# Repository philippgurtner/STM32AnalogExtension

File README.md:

# STM32AnalogExtension
In diesem Repository befinden sich die Daten für eine analog Erweiterung, bestehend aus einem externen ADC für das STM32F0-Discovery Board. 
Im weiteren ist die komplette Dokumentation, so dass die Projektschritte verstanden werden können und auch das Projekt verständlich wird. 

Das Projekt ist OpenSource & darf frei verwendet (und so auch gerne verbessert) werden. 
Ich hoffe viel Freude damit zu bereiten. 
:)

# Projektdokumentation

## Aufgabe
Für die Bereichsübergreifende Projekte der Schule sollte eine Erweiterung für das STM32F051Discovery Kit erstellt werden. 
Dieses Projekt ist eine Analoge Erweiterung mit einem 24Bit 4kSps externen ADC. Dabei ist wichtig dass die Erweiterung mit SPI Angesteuert wird. 
Mehr im Fokus des Projektes stand die Einfachheit, so das das Produkt einfach angewendet werden kann, als es Sehr genau ist. 
So wurde bei der Temperaturmessung auf die Konstantstromquelle Verzichtet, jedoch können zukünftige Anwender die tolle Auflösung mit allen Problemen und Hürden selbst erfahren. 

### Vorgaben
-	Es soll nur eine Seite für Anschlüsse genutzt werden
-	Die Erweiterungsplatine sitzt also zur rechten oder linken Seite des STM32F0-Board
-	Die Seite wird durch die Versorgungsspannung vorgegeben, wenn möglich 3V
-	Platinendicke 1,6mm
-	Lagenanzahl: 2
-	Bestückungsdruck: Schriftgrösse 1mm  Name der Bauteile, Stecker Pin 1, Signalnamen Stecker 
    - 2mm Name Projekt, Datum, Namen der Ersteller
-	Line Space ≥200μm
-	GND-Plane
-	Abmessung Discovery-Board: 33Pin Header

### Zielsetzung
- Das Board muss passend als Erweiterung für das Devboard sein, so dass es einfach adaptiert werden kann. 
- Die Hauptanwendung besteht darin einen 3-Leiter PT100 zu messen.
- Weiter soll möglich sein, durch eine Buchse eine eigene Messspannung hinzuzuführen, so dass auch diese digitalisiert werden kann. 
- Durch einen hochauflösenden ADC (>16Bit) werden dann hohe Genauigkeiten möglich.

## Grundlagen
### Analog-Digital-Converter (ADC)
Die Aufgabe eines ADC’s, ist die Umwandlung von analogen Signalen zu digitalen Daten. Dabei sind mehrere Faktoren wichtig, wie SampleRate und Auflösung (Bittiefe). Um die Signale zu ermitteln müssen wir wissen, was für eine Auflösung der ADC hat. Denn mit diesem, wissen wir wie fein wir das analoge Signal aufteilen können und so die digitalen Werte erhalten. Anhand der SampleRate sehen wir, wie viel Mal der ADC in der Sekunde das analoge Signal maximal abtasten kann. Mit diesen beiden Werten können wir dann in der Software die Werte in unser Signal umrechnen.
### Temperatursensorschaltungen

Um einen Temperatursensor anzuschliessen gibt es verschiedene Möglichkeiten. Diese sind für thermisch abhängige Widerstände, welche als Temperatursensoren funktionieren. Zum Beispiel PT100 oder PT1000. 

#### Zweileiter-Messung
Der Messwiderstand (Temperatursensor) wird über dieselbe Leitung gespiesen wie auch die Temperatur gemessen wird. Daher, dass über die Leitungen ebenfalls etwas Spannung abfällt, wird dieser Fehler nicht mit einberechnet und wird zu einem Messfehler. 
#### Dreileiter- Messung
Bei der Dreileitermessung wird der Messwiderstand über eine zusätzliche Leitung mit Strom versorgt. Daher fällt einerseits der Messfehler der Spannung weg, da die Temperatur über eine unbelastete Leitung gemessen werden kann. Da der Strom I=0A auf der Messleitung ist kann auf der gemeinsamen Leitung der Messfehler herausgerechnet werden -> Siehe Anwendung. 
#### Vierleiter- Messung
Bei einer Vierleitermessung werden der Messstrom und die Messspannung je auf einer separaten Leitung geführt. So kann der Widerstand komplett ohne Spannungsabfall auf der Messleitung gemessen werden.

## Evaluation
###	ADC
Beim Evaluieren eines ADC’s gibt es sehr viele Möglichkeiten. Die wichtigsten Eigenschaften sind Auflösung (Bittiefe) und Geschwindigkeit (Samples per Second). 
Für dieses Projekt spielt die Geschwindigkeit keine grosse Rolle, da Prozesswerte abgefragt werden möchten und es sich nicht um eine Digitalisierung eines hochfrequenten Signals handelt. 
Die Auflösung spielt für dieses Projekt die grössere Rolle. Da gezeigt werden möchte wie genau der ADC ist, soll die Temperatur des Temperatursensors ohne jegliche Verstärkung gemessen werden. 
Die Berechnungen zu der Temperaturauflösung sind in Tabelle 1 zu finden. \todo

### Temperatursensor
Als Temperatursensor eignet sich ein thermisch abhängiger Widerstand sehr gut. Diese werden oft auch in Industrieanlagen verwendet. Da gerade ein fertiger PT100 Sensor an Lager ist wird dieser Verwendet, er benötigt nur eine Buchse auf der Platine um den Sensor anzuhängen. 
###	Weitere Anschlüsse
Als zusätzliche Anschlüsse wurden BNC Buchsen ausgewählt. Durch ihre Standardisierung und häufigen gebrauch eignen sie sich gut um weitere Signale anzulegen und zu messen. 
Es können dann entweder Oszilloskop-Messspitzen oder auch Adapter auf andere Hochfrequenz Stecker, wie auch auf Bananenbuchse verwendet werden. 

## Schaltungsaufbau
### 3-Leitermessung
Für diese Schaltung wird eine Dreileiter-Messung für den Temperatursensor verwendet, da diese sehr einfach aufzubauen, wie auch dann interessant zu verarbeiten ist. Weiter sind hier nur 3 ADC Kanäle nötig obwohl wie bei einer 4-Leiter Messung auch der Widerstand der Messleitung herausgerechnet werden kann.  
### ADC-Serial Interface
Der ADC besitzt ein Serial Peripherie Interface (SPI). Über diese kann mit dem Microcontroller kommuniziert werden. Damit die Peripherie nicht per Bit-Banging angesteuert werden muss, müssen die SPI-Anschlüsse beim Microcontroller an einen SPI fähigen Port geroutet werden.
### Funktion der Schaltung / Überlegungen
Dank folgender Rechnung wird ersichtlich wie die Spannung über dem PT100 berechnet werden kann. Dies funktioniert nach der theoretischen Betrachtung in Abbildung 4.
Es werden hier alle anderen Spannungen herausgerechnet. 

## Auswertung V0.1 
### Hardware
Während der Lötarbeit konnten wir nichts Auffälliges erkennen, was beim Löten problematisch werden könnte. Erst beim Konfigurieren der SPI-Schnittstelle mit der STM32CubeMX-Software, haben wir festgestellt, dass die SPI-Schnittstelle nicht frei auf alle Pins mapbar ist, wie wir das fälschlicherweise aus dem Datenblatt gelesen haben.
Somit müssen am Schema noch einige Anpassungen gemacht werden. Weiter haben wir auch während der Bearbeitung gemerkt, dass der ADC mit Differenzmessung arbeitet. Dies bedeutet, er misst die Differenz zwischen zwei Kanälen. Möchte man eine Spannung absolut messen, so muss dies mit einer Differenzmessung zu Masse erfolgen. Der Chip bietet die Möglichkeit im INPMUX-Register als negative Referenz den AINCOM-Pin zu verwenden, der aber mit Masse verbunden sein sollte.
Für die ersten Versuche mit dem Prototyp haben wir die Kontakte auf der Leiterplatte korrigiert, so dass wir Tests durchführen konnten. Als Erweiterung für die nächste Version wäre zusätzlich eine Stiftleiste vorzusehen, dass die SPI-Analyse einfacher mit einem Logicanalyzer erfolgen kann. Dies hat auch einen Vorteil für den späteren Unterricht, so kann die SPI-Schnittstelle einfacher analysiert werden. 

In der nachfolgenden Tabelle sind die Leiterplattenänderungen festgehalten:

|    WAS                       |    von                 |    Nach                                        |    div.                                                                                                          |
|------------------------------|------------------------|------------------------------------------------|------------------------------------------------------------------------------------------------------------------|
|    Clock                     |    PA4                 |    PA5                                         |    SPI                                                                                                           |
|    MOSI                      |    PA5                 |    PA7                                         |    SPI                                                                                                           |
|    CS                        |    PA7                 |    PF5                                         |    SPI                                                                                                           |
|    AINCOM                    |    Nc                  |    GND                                         |    Differenzmessung                                                                                              |
|    Stiftleiste               |                        |                                                |    Für Debugging / SPI-Analyse                                                                                   |
|    Widerstände   R12-R14     |    Eingang von ADC     |    weglassen                                   |    Können Störungen auf   Messleitung verursachen                                                                |
|    BNC-Abschwächer           |    2.2k Ohm            |    Spannungsteiler mit 47kOhm und   2.2kOhm    |    Somit können Eingangsspannungen   bis zu 50V angelegt werden und nicht nur 2.5V über die Interne Referenz     |
|    5.08mm   schraubklemme    |    Weglassen           |                                                |    So können die Temperatursignale   direkter und präziser geroutet werden. Der Stecker wird nicht benötigt.     |
|    Kondensatoren   1uF       |    AIN0, AIN1, AIN2    |    GND                                         |    Filterung der Temp Messung                                                                                    |
|    Kondensator   1uF         |    AIN0                |    AIN1                                        |    Filterung der Temp Messung                                                                                    |                                                                         |   |

## Softwarerealisierung 
### Konfiguration mit STM32CubeMX
Vorzunehmende Konfigurationen in STM32CubeMX, um die SPI-Schnittstelle zu verwenden: 
Beim Starten das STM32F0-Discovery Board auswählen, so werden die Taster und LEDs richtig initialisiert
-   Pinout & Konfiguration:
    - Pin-Konfiguration
        - PF5: 	ADC_CS
        - PC4: 	ADC_START
        - PC5: 	ADC_RESET
        - PB0: 	ADC_DRDY
    - Modul Connectivity --> SPI1 hinzufügen
        - Data Size: 	8Bit
        - Prescaler:
        - First Bit: 	MSB First
        - Clock Polarity (CPOL): 	LOW
        - Clock Phase (CPHA): 		2 Edge
- Project Manger
    - Code Generator
    - Generate Files: Generate peripheral initialization as a pair... 
        (So wird nicht eine lange main.c-Datei erzeugt)

### Verwenden von HAL-Library 
Hardware Abstraction Librarys, kurz HAL, dienen dazu unabhängig von der verwendeten Hardware, eine Software zu schreiben. So kann eine mit HAL geschriebene Software einfach auf ein anderes System portiert werden und das System übernimmt die Hardwaresteuerung, so dass der Nutzercode nicht (gross) angepasst werden muss. So wird zum Beispiel das Schreiben eines Pins ganz einfach, man muss sich nicht mehr überlegen wo der gerade angeschlossen ist, man benutzt einfach das Userlabel zum Pin. 
```c
HAL_GPIO_WritePin(ADC_CS_GPIO_Port, ADC_CS_Pin,X)
// X=1 --> Ausgang wird auf 1 gesetzt
// X=0 --> Ausgang wird auf 0 gesetzt
```

### SPI-Analyse mit Logicanalyzer

Erweiterungen siehe Anhang
In vielen Fällen kann es hilfreich sein, wenn man mit einem Busprotokoll arbeitet, dieses auch zu messen. Es stand uns dazu ein PicoScope6 zur Verfügung. Sie können bis zu 16 Digitalanalysen und 2 Analoganalysen machen. Es ist ein Oszilloskop ohne Bildschirm. In der Software (Für Windows, MacOS und Linux) kann man das PicoScope steuern. Folgend unsere Erfahrungen. 
Im Anhang befindet sich eine Anleitung wie man eine Analyse der SPI Daten machen kann.

## Softwarefunktionen
Einen kurzen Einblick in die Funktionen welche eingesetzt werden. Weitere Details können dem Code entnommen werden. 
### Registermanipulation
Zum Schreiben und lesen von Registern gibt es die Funktionen (Auszug .h File): 

\todo

Wenn nur ein Register gelesen / geschrieben werden muss, so kann jeweils die ADCreg**** Funktion benutzt werden
### Commands
Der ADC kann über verschiedene Kommandos gesteuert werden. Diese sind alle in der "ADS1204S0x.h" Datei definiert.
```c
void ADCsendCommand(uint8_t op_code);
```
Der Funktion können die Verschiedenen op_codes mitgegeben werden. 

### Berechnungsfunktionen
#### ADC Werte auslesen
Um die Spannung über dem PT100 zu berechnen, werden alle Spannungen der drei ADC`s ausgelesen. Wie hier dargestellt messen die ADC`s folgende Spannungen:

```math
\mathrm{ADC0}=U_{\mathrm{Leiter}}+U_{\mathrm{PT100}}+U_{\mathrm{Leiter}}+U_{\mathrm{Mess}}\bigm\mathrm{ADC1}=U_{\mathrm{Leiter}}+U_{\mathrm{Mess}}\bigm\mathrm{ADC2}=U_{\mathrm{Mess}}\bigmU_{\mathrm{PT100}}=\mathrm{ADC0}-2\times U_{\mathrm{Leiter}}-U_{\mathrm{Mess}}\bigmU_{\mathrm{PT100}}=\mathrm{ADC0}-2\times\left(\mathrm{ADC1}-\mathrm{ADC2}\right)-\mathrm{ADC2\bigm}U_{\mathrm{PT100}}=\mathrm{ADC0}-2\times\mathrm{ADC1}+\mathrm{ADC2}
```
### Dimensionierungen und Berechnungen
Als Temperatursensor wird ein PT100 verwendet. Nach Spezifikation hat der Temperatursensor bei 0°C einen 100Ω Widerstand. Je nach Temperatur verändert sich der Widerstand, nach einer bestimmten Kurve. 
Als Messstrom wird bei 0°C 0.5mA verwendet. Da sich der Temperatursensor selbst erwärmt darf dieser Messstrom nicht zu hoch gewählt werden.
Um den geflossenen Strom durch den ADC zu messen, wird über einem präzisen Referenzwiderstand die Spannung gemessen, welche vom Messstrom erzeugt wird.

Anschlüsse:
Es wurde eine Temperaturmessung mittels PT100 3-Leiter Widerstand vorgenommen. 
Als zusätzliche Anschlüsse wurden BNC Buchsen ausgewählt. Durch ihre Stndrdisierung und often gebrauch eignen sie sich um weitere Signale anzulegen und zu messen. 

# Schaltungsaufbau
## ADC-Serial Interface
Der ADC besitzt ein Serial Peripherie Interface (SPI). Über dies kann mit dem Microntroller Komunizieren. 
Damit die Peripherie nicht per Bit-Banging angesteuert werden muss, müssen sie beim Microcontroller mit bei einem SPI fähigen Port verbunden werden.
# Dimensionierung
Als Temperatursensor wird ein TP100 verwendet. Nach Spezifikation hat der Temperatursensor bei 0°C 100R Widerstand. Je nach Temperaturänderung verändert sich der Widerstand nach einer Spezifizierten Kurve. 
Als Messstrom wird bei 0°C 0.5mA verwendet. Da sich der Temperatursensor selbst erwärmt darf dieser Messstrom nicht zu hoch gewählt werden. 

Um den Geflossenen Strom durch den ADC zu messen wird über einem Refererenzwiderstand die Spannung gemessen welche vom Messstrom erzeugt wird. 

# Einführung Picoscope

Das Picoscope ist ein Logicanalyser. Mit ihm ist es Möglich mehrere Digitale Signale zu Analysieren und die Daten auszuwerten. Um Herauszufinden ob die Serielle Kommunikation richtig Funktioniert kann man mit diesem Hilfsmittel einfacher messen und die Daten analysieren. 

## Vorbereitung

Um Das Picoscope an einem PC benutzen zu können sind einige Schritte notwendig. 

### Installieren der Software

Die Software kann auf der Webseite von Picosope unter > Downloads heruntergeladen werden. 
Hier muss die Genaue Modelbezeichung angegeben werden. (Wir verwendeten das Picoscope der Schule [*PicoScope 2206B MSO*](https://www.picotech.com/downloads/_lightbox/picoscope-6))

### Anschliessen der Digitalen Kanäle

Die Digitalen Kanäle befinden sich beim 16-Pin Stecker in der Mitte. Das Mitgelieferte Kabel dient um mit dem UC Board zu verbinden. 

### Einrichten der Software

1. Digitale Kanäle Gruppen

   1. Kanal Auswählen

   2. Kanal intelligent benennen

2. Hinzufügen eines Seriellen Encoders:

   1. Werkzeuge > Serielle Entschlüsselung -> Erstellen > SPI >

3. Setzen des Triggers (In der untersten Leiste)
   1. Trigger: Einzeln
   2. In den Triggereinstellungen (Rechts vom Trigger) kann auf Digital > CS Pos Flanke gesetzt werden
   3. Start

## SPI Analyse

Mit den Empfangen Daten lässt sich verstehen was in SPI gesendet wird

Folgend im Code und Als Analyse:

MISO, Die Daten werden vom Master an den Slave gesendet. Die Rückgabe des Slaves ist nicht wichtig. 

```c
HAL_GPIO_WritePin(ADC_CS_GPIO_Port, ADC_CS_Pin,0);

uint8_t au8_txdata = {0x42,		// Register INPMUX_REG_ADDR (0x02) | Write command 0x40
                      0,		// Write length -1 = 0
                      0x3C};	// Data = ADS_P_AIN3 (0x30)+ ADS_N_AINCOM (0x0C)		
HAL_SPI_Transmit(&hspi1,au8_txdata,3,10);
HAL_GPIO_WritePin(ADC_CS_GPIO_Port, ADC_CS_Pin,1);
```

# Variablen Viewer installieren (debuggen)

Das STMStudio ermöglicht es eine *debug Datei zu Importieren und diese Laufen zu lassen. So können mehrere globale Variablen angesehen werden. So kann eine Langzeitanalyse des Verhalten gemacht werden. 

- STM-STUDIO-STM32 (von https://www.st.com/en/development-tools/stm-studio-stm32.html ) installieren (benötigt Java https://www.java.com/de/download/win10.jsp)

- STM Studio öffnen

- "File" > "Import variables from executable" öffnen
  - "Executable file" .elf Datei suchen (im STM Projekt unter "Debugger")
  - (Warnung Ignorieren)
  - Variable zum Monitoren auswählen 
  - "Import" , "Close"

- Variable (Display Variables) in Viewer hineinziehen (Drag and Drop)

- Start Knopf drücken (Debugger aus IDE darf nicht gleichzeitig aktiv sein)

- Im Viewer: Rechtsklick, "Autorange" > "Both Axis"

- Eventuell als Balken darstellen, maximum wert beachten (über hex ganz einfach manuell einstellbar)

# Sorry, die vollständige Dokumentation ist Leider nicht Opensource (und vorallem .docx), jedoch wird das Projekt bei Gelegenheit hier noch zu ende Dokumentiert (natürlich in MD :) , Danke für die Geduld)

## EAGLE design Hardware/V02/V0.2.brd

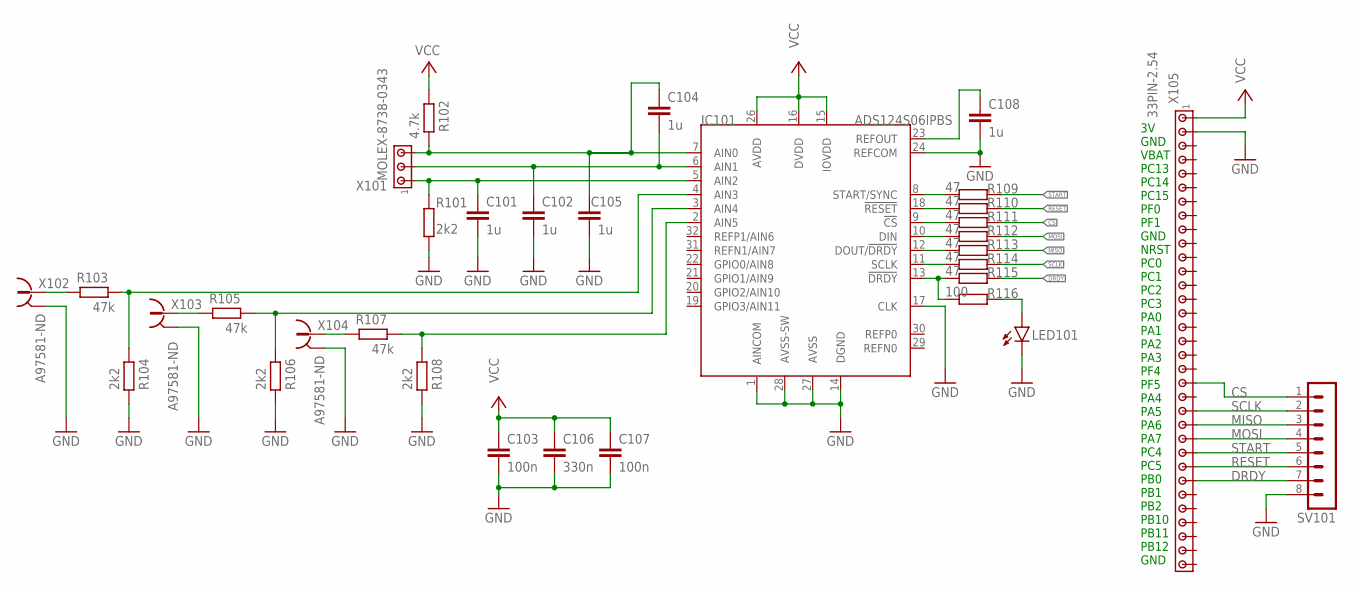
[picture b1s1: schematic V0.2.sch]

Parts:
C101, C102, C104, C105, C108: 1u; C0603; DIGIKEY_NR 1276-1182-1-ND
C103, C107: 100n; C0603; DIGIKEY_NR 1276-6439-1-ND
C106: 330n; C0603; DIGIKEY_NR 490-6050-1-ND
IC101: ADS124S06IPBS; TQFP32-05; DIGIKEY_NR 296-45188-ND
LED101: LEDSML0603; SML0603; DIGIKEY_NR 475-3118-1-ND
R101, R104, R106, R108: 2k2; R0805W; DIGIKEY_NR 408-1635-1-ND
R102: 4.7k; R0603; DIGIKEY_NR 311-4.70KHRCT-ND
R103, R105, R107: 47k; R0603; DIGIKEY_NR P123333CT-ND
R109, R110, R111, R112, R113, R114, R115: 47; R0603; DIGIKEY_NR 311-470GRCT-ND
R116: 100; R0603; DIGIKEY_NR 311-100DCT-ND
SV101: MA08-1; DIGIKEY_NR 732-5321-ND
X101: MOLEX-8738-0343; MOLEX-87438-0343; DIGIKEY_NR WM7647CT-ND
X102, X103, X104: A97581-ND; 1634503; DIGIKEY_NR A97581-ND
X105: 33PIN-2.54; 1X33; DIGIKEY_NR 609-2223-ND

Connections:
AIN0: C104.1, C105.1, IC101.7 (AIN0), R102.1, X101.3, X101.3_1 (3)
AIN1: C102.1, C104.2, IC101.6 (AIN1), X101.2, X101.2_1 (2)
AIN2: C101.1, IC101.5 (AIN2), R101.2, X101.1, X101.1_1 (1)
CS: R111.2, SV101.1, X105.20
DRDY: R115.2, SV101.7, X105.27
GND: C101.2, C102.2, C103.2, C105.2, C106.2, C107.2, C108.2, IC101.1 (AINCOM), IC101.14 (DGND), IC101.17 (CLK), IC101.24 (REFCOM), IC101.27 (AVSS), IC101.28 (AVSS-SW), LED101.C, R101.1, R104.1, R106.1, R108.1, SV101.8, X102.2, X102.3 (2), X102.4 (2), X102.5 (2), X103.2, X103.3 (2), X103.4 (2), X103.5 (2), X104.2, X104.3 (2), X104.4 (2), X104.5 (2), X105.2
MISO: R113.2, SV101.3, X105.23
MOSI: R112.2, SV101.4, X105.24
unnamed: IC101.8 (START/SYNC), R109.1
unnamed: IC101.18 (!RESET), R110.1
unnamed: IC101.9 (!CS), R111.1
unnamed: IC101.10 (DIN), R112.1
unnamed: IC101.12 (DOUT/!DRDY), R113.1
unnamed: IC101.11 (SCLK), R114.1
unnamed: IC101.13 (!DRDY), R115.1, R116.1
unnamed: IC101.4 (AIN3), R103.1, R104.2
unnamed: R103.2, X102.1
unnamed: R105.2, X103.1
unnamed: LED101.A, R116.2
unnamed: C108.1, IC101.23 (REFOUT)
unnamed: R107.2, X104.1
unnamed: IC101.3 (AIN4), R105.1, R106.2
unnamed: IC101.2 (AIN5), R107.1, R108.2
RESET: R110.2, SV101.6, X105.26
SCLK: R114.2, SV101.2, X105.22
START: R109.2, SV101.5, X105.25
VCC: C103.1, C106.1, C107.1, IC101.15 (IOVDD), IC101.16 (DVDD), IC101.26 (AVDD), R102.2, X105.1

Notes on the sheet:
3V GND VBAT PC13 PC14 PC15 PF0 PF1 GND NRST PC0 PC1 PC2 PC3 PA0 PA1 PA2 PA3 PF4 PF5 PA4 PA5 PA6 PA7 PC4 PC5 PB0 PB1 PB2 PB10 PB11 PB12 GND

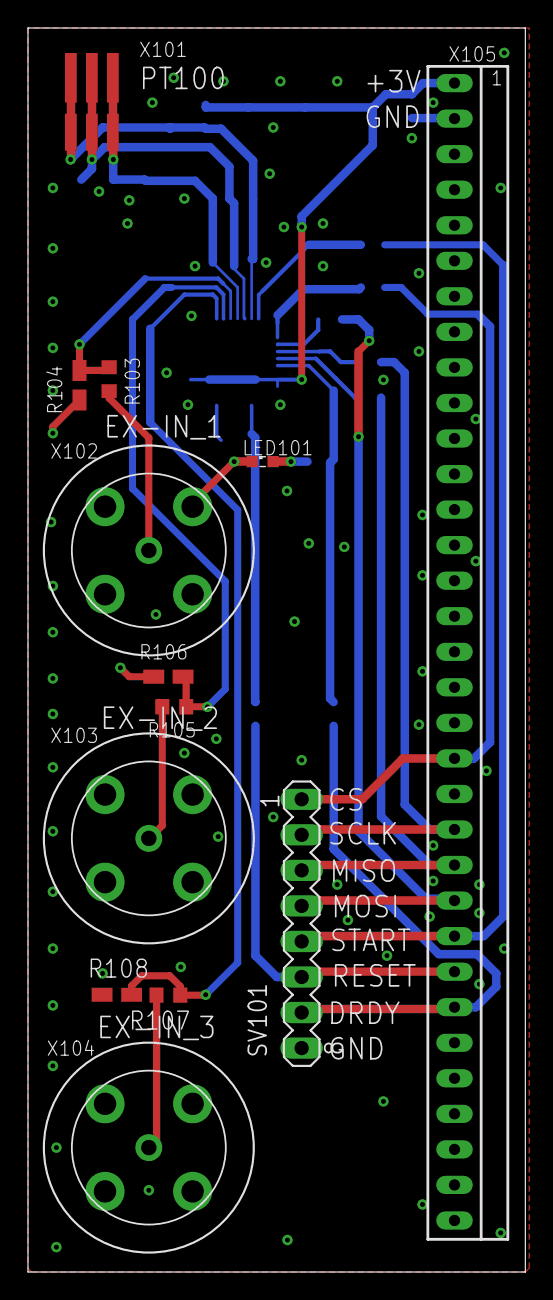
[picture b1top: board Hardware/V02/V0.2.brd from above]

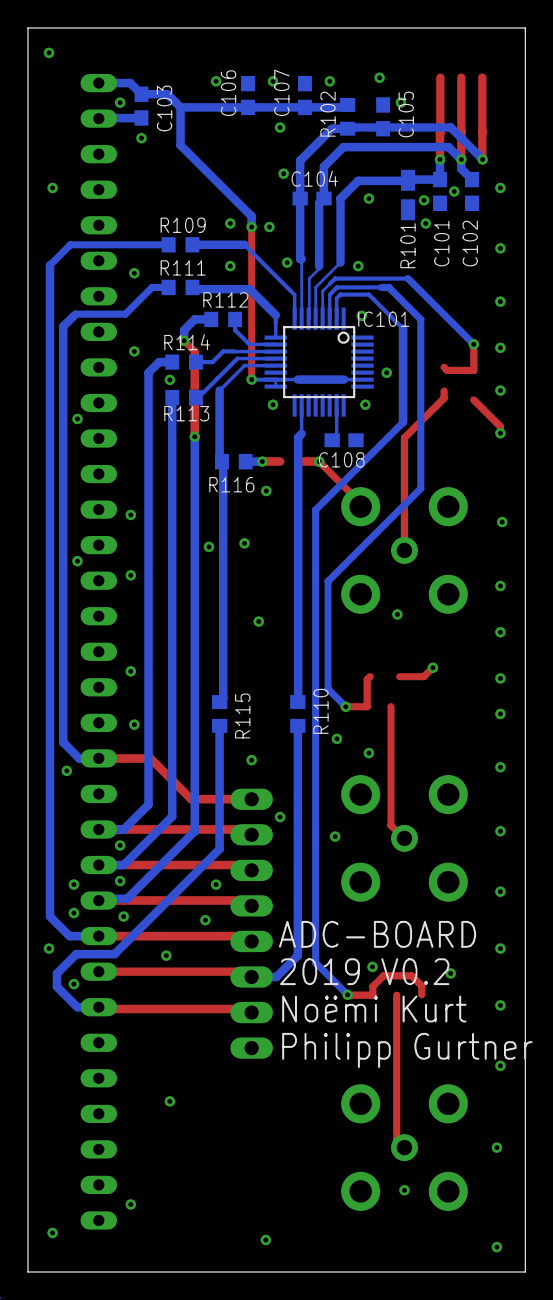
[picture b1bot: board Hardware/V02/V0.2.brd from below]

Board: 2 copper layers, 35.5 x 88.9 mm, 32 parts (19 on the bottom side), 27 nets.

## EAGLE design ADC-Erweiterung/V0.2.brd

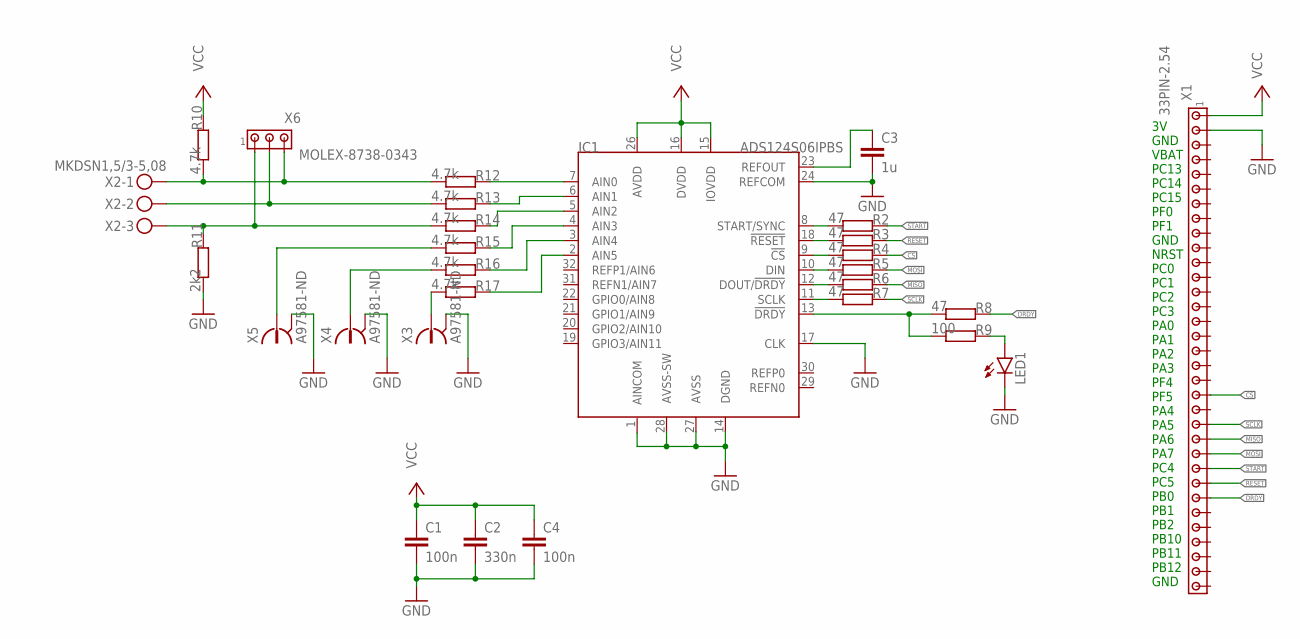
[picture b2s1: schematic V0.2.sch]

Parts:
C1, C4: 100n; C0603; DIGIKEY_NR 1276-6439-1-ND
C2: 330n; C0603; DIGIKEY_NR 490-6050-1-ND
C3: 1u; C0603; DIGIKEY_NR 1276-1182-1-ND
IC1: ADS124S06IPBS; TQFP32-05; DIGIKEY_NR 296-45188-ND
LED1: LEDSML0603; SML0603; DIGIKEY_NR 475-3118-1-ND
R2, R3, R4, R5, R6, R7, R8: 47; R0603; DIGIKEY_NR 311-470GRCT-ND
R9: 100; R0603; DIGIKEY_NR 311-100DCT-ND
R10, R12, R13, R14, R15, R16, R17: 4.7k; R0603; DIGIKEY_NR 311-4.70KHRCT-ND
R11: 2k2; R0805W; DIGIKEY_NR 408-1635-1-ND
X1: 33PIN-2.54; 1X33; DIGIKEY_NR 609-2223-ND
X2: MKDSN1,5/3-5,08; DIGIKEY_NR 277-14503-ND
X3, X4, X5: A97581-ND; 1634503; DIGIKEY_NR A97581-ND
X6: MOLEX-8738-0343; MOLEX-87438-0343; DIGIKEY_NR WM7647CT-ND

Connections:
CS: R4.2, X1.20
DRDY: R8.2, X1.27
GND: C1.2, C2.2, C3.2, C4.2, IC1.1 (AINCOM), IC1.14 (DGND), IC1.17 (CLK), IC1.24 (REFCOM), IC1.27 (AVSS), IC1.28 (AVSS-SW), LED1.C, R11.1, X1.2, X3.2, X3.3 (2), X3.4 (2), X3.5 (2), X4.2, X4.3 (2), X4.4 (2), X4.5 (2), X5.2, X5.3 (2), X5.4 (2), X5.5 (2)
MISO: R6.2, X1.23
MOSI: R5.2, X1.24
unnamed: IC1.8 (START/SYNC), R2.1
unnamed: IC1.18 (!RESET), R3.1
unnamed: IC1.9 (!CS), R4.1
unnamed: IC1.10 (DIN), R5.1
unnamed: IC1.12 (DOUT/!DRDY), R6.1
unnamed: IC1.11 (SCLK), R7.1
unnamed: IC1.13 (!DRDY), R8.1, R9.1
unnamed: R10.1, R12.1, X2.1, X6.3, X6.3_1 (3)
unnamed: R13.1, X2.2, X6.2, X6.2_1 (2)
unnamed: R11.2, R14.1, X2.3, X6.1, X6.1_1 (1)
unnamed: R15.1, X5.1
unnamed: IC1.3 (AIN4), R16.2
unnamed: IC1.2 (AIN5), R17.2
unnamed: LED1.A, R9.2
unnamed: C3.1, IC1.23 (REFOUT)
unnamed: IC1.4 (AIN3), R15.2
unnamed: R16.1, X4.1
unnamed: R17.1, X3.1
unnamed: IC1.5 (AIN2), R14.2
unnamed: IC1.7 (AIN0), R12.2
unnamed: IC1.6 (AIN1), R13.2
RESET: R3.2, X1.26
SCLK: R7.2, X1.22
START: R2.2, X1.25
VCC: C1.1, C2.1, C4.1, IC1.15 (IOVDD), IC1.16 (DVDD), IC1.26 (AVDD), R10.2, X1.1

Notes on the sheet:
3V GND VBAT PC13 PC14 PC15 PF0 PF1 GND NRST PC0 PC1 PC2 PC3 PA0 PA1 PA2 PA3 PF4 PF5 PA4 PA5 PA6 PA7 PC4 PC5 PB0 PB1 PB2 PB10 PB11 PB12 GND

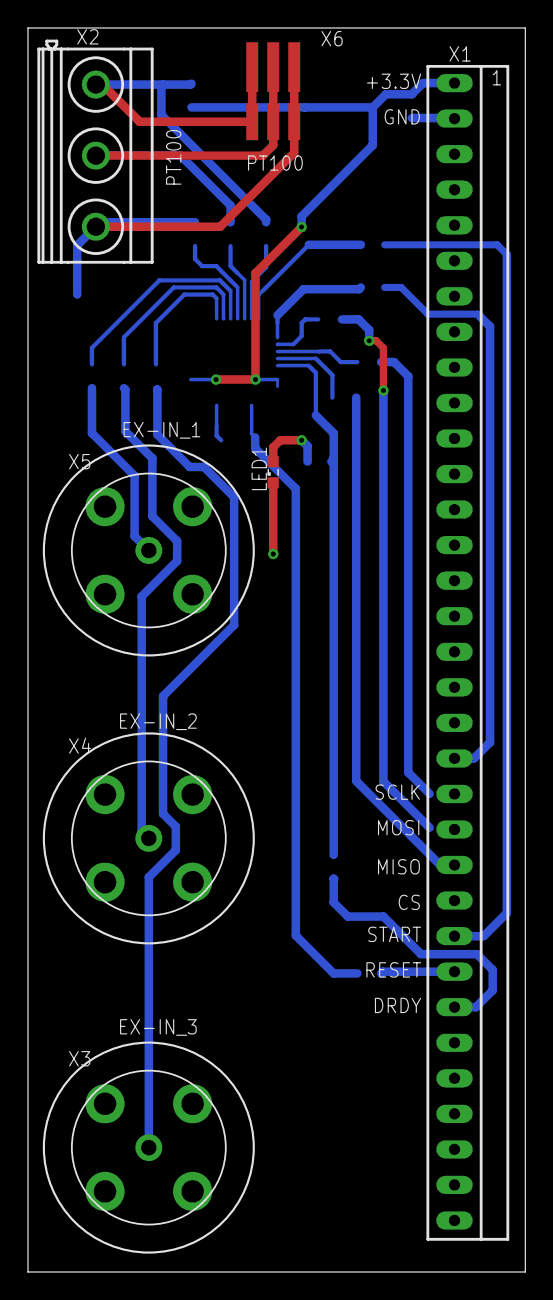
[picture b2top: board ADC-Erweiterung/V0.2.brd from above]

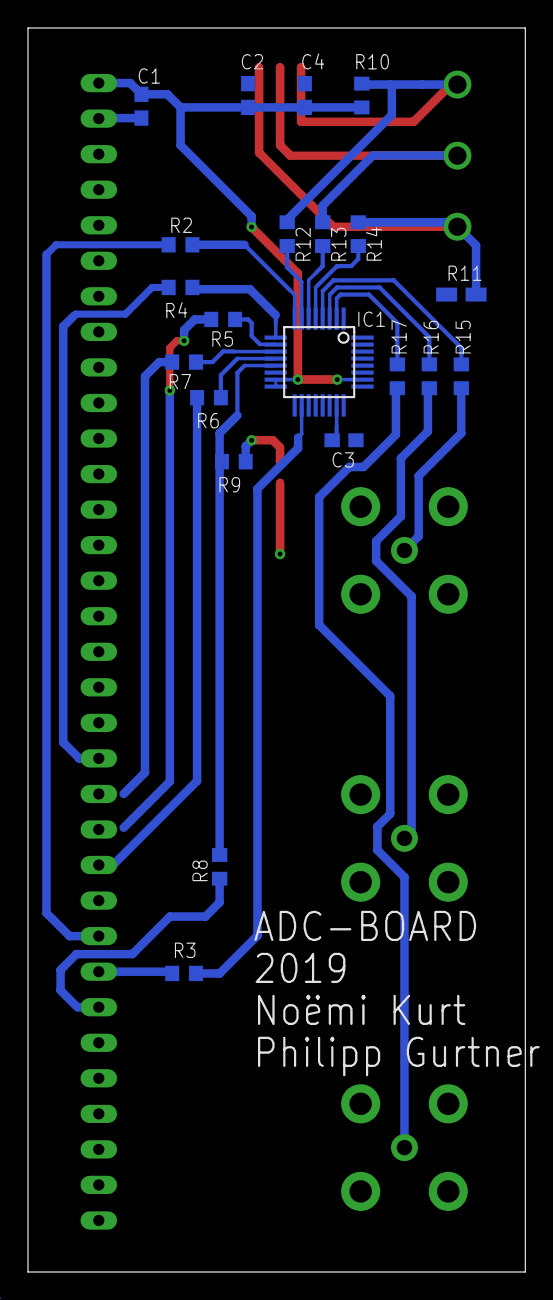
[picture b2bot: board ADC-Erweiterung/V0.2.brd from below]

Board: 2 copper layers, 35.5 x 88.9 mm, 28 parts (21 on the bottom side), 30 nets.

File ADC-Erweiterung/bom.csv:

"Qty";"Value";"Device";"Package";"Parts";"Description";"DIGIKEY_NR";"DIGIKEY_PRICE";"SPICEPREFIX";
"1";"";"LEDSML0603";"SML0603";"LED1";"LED";"475-3118-1-ND ";"0.52";"";
"1";"100";"R-EU_R0603";"R0603";"R9";"RESISTOR, European symbol";"311-100DCT-ND";"0.20";"R";
"1";"100n";"C-EUC0603";"C0603";"C4";"CAPACITOR, European symbol";"1276-6439-1-ND ";"0.10";"C";
"1";"100n";"C-EUC0603";"C0603";"C1";"CAPACITOR, European symbol";"1276-6439-1-ND";"0.10";"C";
"1";"1u";"C-EUC0603";"C0603";"C3";"CAPACITOR, European symbol";"1276-1182-1-ND";"0.10";"C";
"1";"2k2";"R-EU_R0805W";"R0805W";"R11";"RESISTOR, European symbol";"408-1635-1-ND";"4.37";"R";
"1";"330n";"C-EUC0603";"C0603";"C2";"CAPACITOR, European symbol";"490-6050-1-ND";"0.22";"C";
"1";"33PIN-2.54";"33PIN-2.54";"1X33";"X1";"";"609-2223-ND ";"1.41";"";
"7";"4.7k";"R-EU_R0603";"R0603";"R10, R12, R13, R14, R15, R16, R17";"RESISTOR, European symbol";"311-4.70KHRCT-ND";"0.10";"R";
"7";"47";"R-EU_R0603";"R0603";"R2, R3, R4, R5, R6, R7, R8";"RESISTOR, European symbol";"311-470GRCT-ND";"0.10";"R";
"3";"A97581-ND";"A97581-ND";"1634503";"X3, X4, X5";"";"A97581-ND";"1.73";"";
"1";"ADS124S06IPBS";"ADS124S0XIPBS";"TQFP32-05";"IC1";"";"296-45188-ND";"10.15";"";
"1";"MKDSN1,5/3-5,08";"MKDSN1,5/3-5,08";"MKDSN1,5/3-5,08";"X2";"MKDSN 1,5/ 3-5,08 Printklemme";"277-14503-ND";"1.57";"";
"1";"MOLEX-8738-0343";"MOLEX-8738-0343";"MOLEX-87438-0343";"X6";"";"WM7647CT-ND";"0.81";"";

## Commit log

2019-04-03 add EagleFiles
2019-04-11 11.4
2019-05-03 2.5.19_BUP:)
2019-05-09 ADD Doku
2019-05-23 finished
2019-05-23 Rename Eagle.gitignore to .gitignore
2019-06-06 Stand der Abgabe
2019-08-29 add Programmierung & Verbesserung
2019-09-19 Software Start & Aufgeräumt
2019-10-16 ...idk
2019-10-21 schönner Programiert
2019-12-03 AlotofImprouvement
2019-12-03 SchemativV02
2019-12-03 AbgabeSoftware
2019-12-03 improuveschematic
2019-12-04 Dokumentation
2019-12-04 easyword
2019-12-04 Finish V02
    New order of hardwarefiles
2019-12-04 V02
    Finish, delet last large files
2019-12-10 Update README.md
    Let's go Doku
2019-12-10 Schemaänderung; BNC-Abschwächer
2020-01-07 Add Dokumentation
